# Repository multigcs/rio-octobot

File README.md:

# rio-octobot
8Axis LinuxCNC-RIO main-board - for the iceWerx iCE40-HX8K FPGA-Devboard - kicad project 
 
experimental - not fully tested yet

## software / gateware
https://github.com/multigcs/riocore

## BOM
https://eu.robotshop.com/de/products/devantech-icewerx-ice40-hx8k-fpga

https://www.amazon.de/WT32-ETH01-Embedded-Schnittstelle-Bluetooth-Entwicklungsplatine/dp/B0CW3DDWZ4

## Forum
German: https://www.cnc-aus-holz.at/index.php?thread/3130-experimente-mit-linux-cnc-auf-raspi-und-ice40-fpga-als-mesa-alternative/&postID=40335#post40335
English: https://forum.linuxcnc.org/18-computer/49142-linuxcnc-rio-realtimeio-for-linuxcnc-based-on-fpga-ice40-ecp5

## Videos

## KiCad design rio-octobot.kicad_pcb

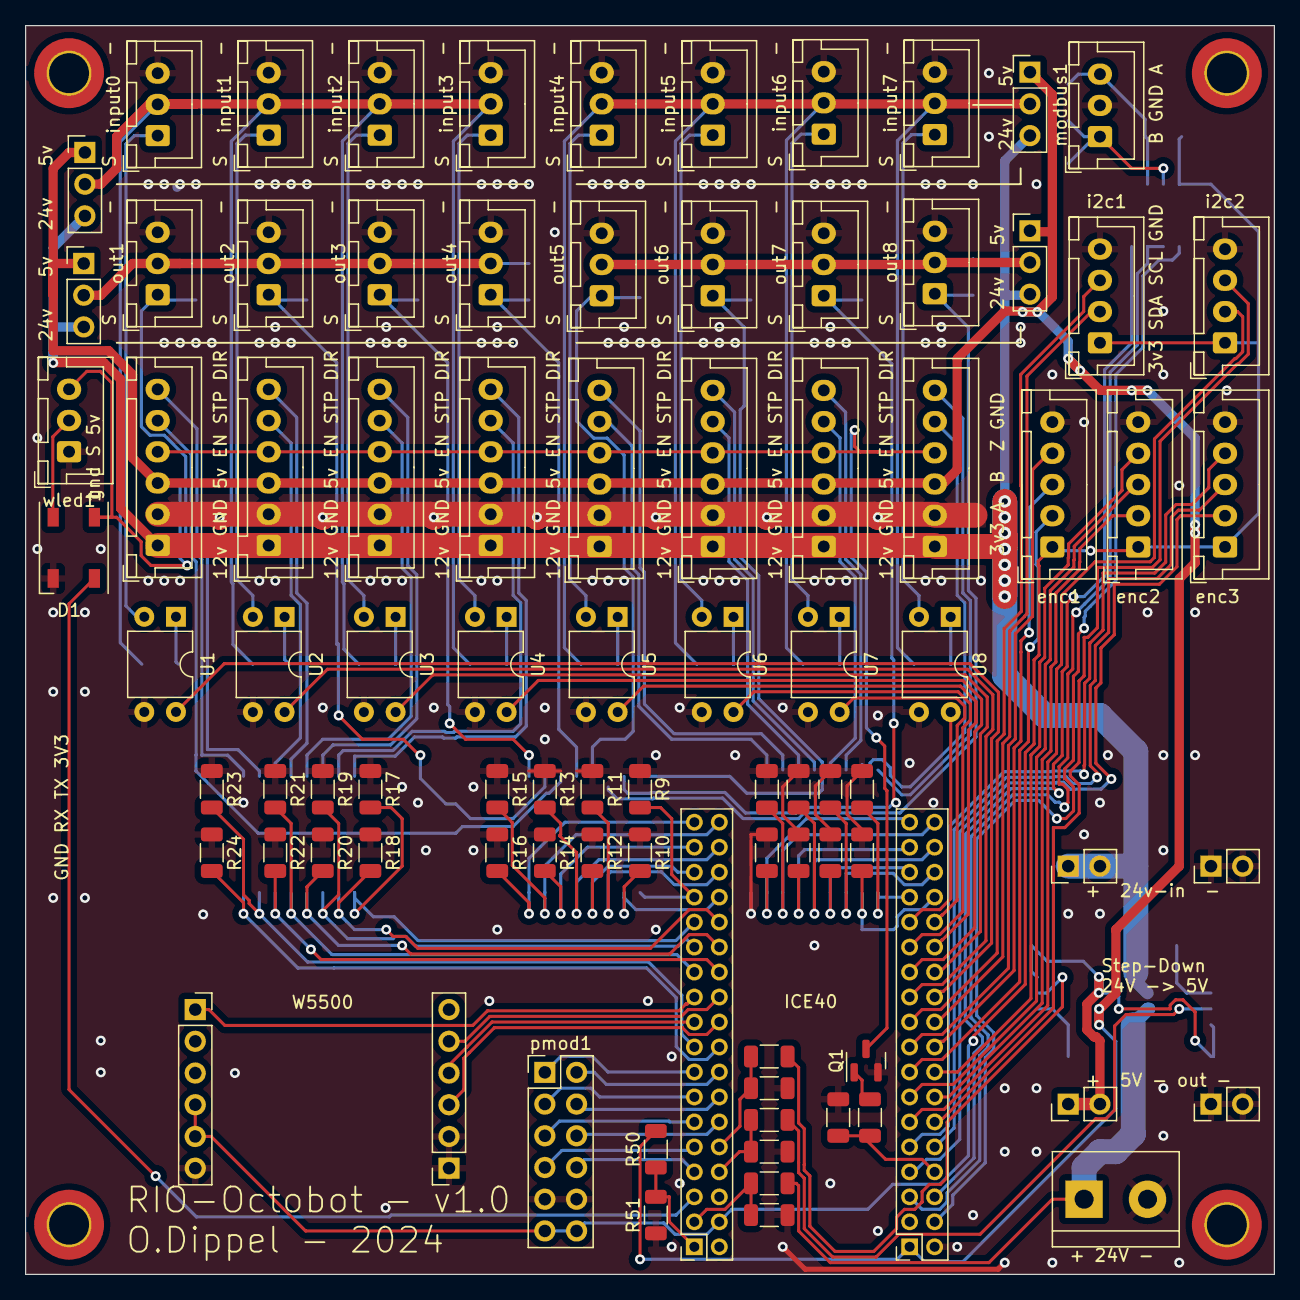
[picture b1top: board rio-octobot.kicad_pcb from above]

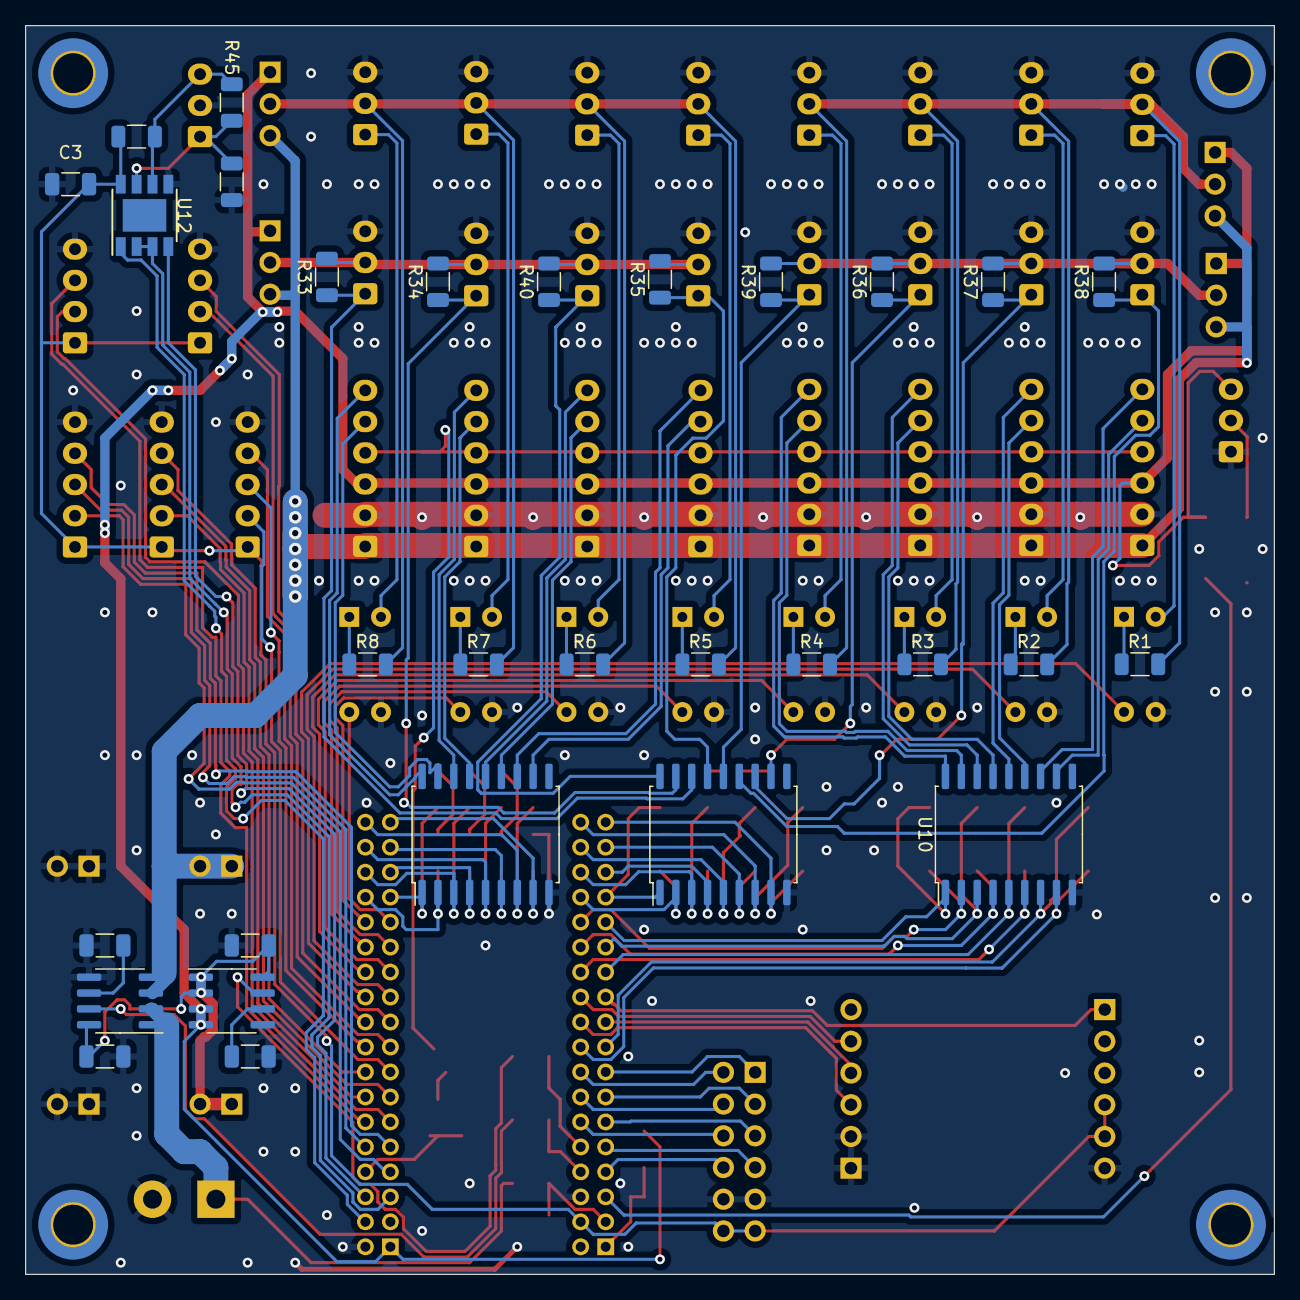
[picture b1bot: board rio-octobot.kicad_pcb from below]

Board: 2 copper layers, 100.0 x 100.0 mm, 123 parts (30 on the bottom side), 125 nets.

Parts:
+24V-1: Screw_Terminal_01x02; TerminalBlock_bornier-2_P5.08mm
C1, C4: 1n; C_1206_3216Metric
C2, C3, C5: 100n; C_1206_3216Metric
D1: WS2812B; LED_WS2812B_PLCC4_5.0x5.0mm_P3.2mm
H1, H2, H3, H4: MountingHole; MountingHole_3.2mm_M3_DIN965_Pad_TopBottom
J1, J2, J3, J4, J5, J6, J7, J8: Conn_01x06; JST_XH_B6B-XH-A_1x06_P2.50mm_Vertical
J9, J10, J11, J12: Conn_01x03; PinHeader_1x03_P2.54mm_Vertical
J15, J16: Conn_01x06; PinSocket_1x06_P2.54mm_Vertical
Q1: BC817; SOT-23
R1, R2, R3, R4, R5, R6, R7, R8, R33, R34, R35, R36, R37, R38, R39, R40: 3k3; R_1206_3216Metric
R9, R10, R11, R12, R13, R14, R15, R16, R17, R18, R19, R20, R21, R22, R23, R24, R55: 10k; R_1206_3216Metric
R25, R26, R27, R28, R29, R30, R31, R32: R; R_1206_3216Metric
R41, R44, R46, R47, R48, R50, R51, R53, R54: 20k; R_1206_3216Metric
R42, R43: 1k; R_1206_3216Metric
R45: 120; R_1206_3216Metric
U1, U2, U3, U4, U5, U6, U7, U8: PC817; DIP-4_W7.62mm
U9, U10, U11: ULN2803A; SOIC-18W_7.5x11.6mm_P1.27mm
U12: MAX485E; Diodes_SO-8EP
U13: ACS712xLCTR-20A; SOIC-8_3.9x4.9mm_P1.27mm
U14: ACS712xLCTR-5A; SOIC-8_3.9x4.9mm_P1.27mm
enc1, enc2, enc3: Conn_01x05; JST_XH_B5B-XH-A_1x05_P2.50mm_Vertical
i2c1, i2c2: Conn_01x04; JST_XH_B4B-XH-A_1x04_P2.50mm_Vertical
in+1: Conn_01x02; PinHeader_1x02_P2.54mm_Vertical
in-1: Conn_01x02; PinHeader_1x02_P2.54mm_Vertical
input0, input1, input2, input3, input4, input5, input6, input7: Conn_01x03; JST_XH_B3B-XH-A_1x03_P2.50mm_Vertical
modbus1: Conn_01x03; JST_XH_B3B-XH-A_1x03_P2.50mm_Vertical
out1, out2, out3, out4, out5, out6, out7, out8: Conn_01x03; JST_XH_B3B-XH-A_1x03_P2.50mm_Vertical
out+1: Conn_01x02; PinHeader_1x02_P2.54mm_Vertical
out-1: Conn_01x02; PinHeader_1x02_P2.54mm_Vertical
pl2, pl3: Conn_02x18_Odd_Even; PinSocket_2x18_P2.00mm_Vertical
pmod1: Conn_02x06_Odd_Even; PinHeader_2x06_P2.54mm_Vertical
wled1: Conn_01x03; JST_XH_B3B-XH-A_1x03_P2.50mm_Vertical

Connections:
3v3: C3.1, J15.4, J15.5, R46.1, U12.8 (VCC), enc1.1, enc2.1, enc3.1, i2c1.1, i2c2.1, pl2.4, pmod1.11, pmod1.12
5v: D1.1 (VDD), J1.3, J2.3, J3.3, J4.3, J5.3, J6.3, J7.3, J8.3, J9.1, J10.1, J11.1, J12.1, R50.2, U14.3 (IP-), U14.4 (IP-), pl3.1, wled1.3
12v: J1.1, J2.1, J3.1, J4.1, J5.1, J6.1, J7.1, J8.1, J9.3, J10.3, J11.3, J12.3, U13.3 (IP-), U13.4 (IP-), in+1.1, in+1.2
/input0/power: J9.2, R1.2, R2.2, R3.2, R4.2, input0.2, input1.2, input2.2, input3.2
/input4/power: J10.2, R5.2, R6.2, R7.2, R8.2, input4.2, input5.2, input6.2, input7.2
unnamed: +24V-1.1, R41.2, U13.1 (IP+), U13.2 (IP+)
unnamed: D1.2 (DOUT), wled1.2
unnamed: J1.4, J2.4, J3.4, J4.4, J5.4, J6.4, J7.4, J8.4, Q1.3 (C)
unnamed: J1.5, U10.11 (O8)
unnamed: J1.6, U10.12 (O7)
unnamed: J2.5, U10.13 (O6)
unnamed: J2.6, U10.14 (O5)
unnamed: J3.5, U10.15 (O4)
unnamed: J3.6, U10.16 (O3)
unnamed: J4.5, U10.17 (O2)
unnamed: J4.6, U10.18 (O1)
unnamed: J5.5, U11.11 (O8)
unnamed: J5.6, U11.12 (O7)
unnamed: J6.5, U11.13 (O6)
unnamed: J6.6, U11.14 (O5)
unnamed: J7.5, U11.15 (O4)
unnamed: J7.6, U11.16 (O3)
unnamed: J8.5, U11.17 (O2)
unnamed: J8.6, U11.18 (O1)
unnamed: J11.2, R36.2, R37.2, R38.2, R39.2, out1.2, out2.2, out3.2, out4.2
unnamed: J12.2, R33.2, R34.2, R35.2, R40.2, out5.2, out6.2, out7.2, out8.2
unnamed: Q1.1 (B), R43.2
unnamed: R1.1, U1.1
unnamed: R2.1, U2.1
unnamed: R3.1, U3.1
unnamed: R4.1, U4.1
unnamed: R5.1, U5.1
unnamed: R6.1, U6.1
unnamed: R7.1, U7.1
unnamed: R8.1, U8.1
unnamed: R40.1, U9.18 (O1), out6.1
unnamed: R34.1, U9.17 (O2), out7.1
unnamed: R33.1, U9.16 (O3), out8.1
unnamed: R35.1, U9.15 (O4), out5.1
unnamed: R39.1, U9.14 (O5), out4.1
unnamed: R38.1, U9.13 (O6), out1.1
unnamed: R37.1, U9.12 (O7), out2.1
unnamed: R36.1, U9.11 (O8), out3.1
unnamed: R45.1, R46.2, U12.6 (A), modbus1.3
unnamed: R44.1, R45.2, U12.7 (B), modbus1.1
unnamed: C1.1, U13.6 (FILTER)
unnamed: C2.1, C5.1, U13.8 (VCC), U14.1 (IP+), U14.2 (IP+), U14.8 (VCC), out+1.1, out+1.2
unnamed: R47.1, U13.7 (VIOUT)
unnamed: C4.1, U14.6 (FILTER)
unnamed: R53.1, U14.7 (VIOUT)
unnamed: U1.2, input0.1
unnamed: U2.2, input1.1
unnamed: U3.2, input2.1
unnamed: U4.2, input3.1
unnamed: U5.2, input4.1
unnamed: U6.2, input5.1
unnamed: U7.2, input6.1
unnamed: U8.2, input7.1
a1: R12.2, U9.4 (I4), pl2.31
a2: R11.2, U9.3 (I3), pl2.32
a3: R14.2, U9.6 (I6), pl2.33
a4: R16.2, U9.8 (I8), pl2.35
a6: R31.2, U11.7 (I7), pl3.36
a7: R32.2, U11.8 (I8), pl3.35
a10: R25.2, U11.1 (I1), pl3.29
a11: U6.4, pl3.25
a12: U5.4, pl3.26
ad1: R47.2, R48.2, pl2.8
ad2: R53.2, R54.2, pl2.10
ad3: R50.1, R51.2, pl2.1
ad4: R41.1, R42.2, pl2.3
b1: R10.2, U9.2 (I2), pl2.30
b14: U4.4, pl3.23
c1: R17.2, U10.1 (I1), pl2.27
c3: R9.2, U9.1 (I1), pl2.29
c4: R13.2, U9.5 (I5), pl2.34
c5: R15.2, U9.7 (I7), pl2.36
c6: R29.2, U11.5 (I5), pl3.34
c7: R30.2, U11.6 (I6), pl3.33
c10: U8.4, pl3.27
c11: U7.4, pl3.28
c12: U2.4, pl3.21
c14: U3.4, pl3.24
d1: R20.2, U10.4 (I4), pl2.26
d3: R18.2, U10.2 (I2), pl2.28
d6: R28.2, U11.4 (I4), pl3.31
d7: R27.2, U11.3 (I3), pl3.32
d10: R26.2, U11.2 (I2), pl3.30
d12: i2c1.3, pl3.19
d14: U1.4, pl3.22
e1: R19.2, U10.3 (I3), pl2.25
e12: enc1.4, pl3.17
e14: i2c1.2, pl3.20
f3: R22.2, U10.6 (I6), pl2.24
f12: enc1.2, pl3.15
f14: enc1.3, pl3.18
g1: R21.2, U10.5 (I5), pl2.23
g3: J16.5, pl2.22
g12: enc2.3, pl3.13
g14: enc2.4, pl3.16
gnd: +24V-1.2, C1.2, C2.2, C3.2, C4.2, C5.2, D1.3 (VSS), J1.2, J2.2, J3.2, J4.2, J5.2, J6.2, J7.2, J8.2, J15.6, J16.1, J16.2, Q1.2 (E), R9.1, R10.1, R11.1, R12.1, R13.1, R14.1, R15.1, R16.1, R17.1, R18.1, R19.1, R20.1, R21.1, R22.1, R23.1, R24.1, R25.1, R26.1, R27.1, R28.1, R29.1, R30.1, R31.1, R32.1, R42.1, R44.2, R48.1, R51.1, R54.1, R55.1, U1.3, U2.3, U3.3, U4.3, U5.3, U6.3, U7.3, U8.3, U9.9 (GND), U10.9 (GND), U11.9 (GND), U12.5 (GND), U13.5 (GND), U14.5 (GND), enc1.5, enc2.5, enc3.5, i2c1.4, i2c2.4, in-1.1, in-1.2, input0.3, input1.3, input2.3, input3.3, input4.3, input5.3, input6.3, input7.3, modbus1.2, out1.3, out2.3, out3.3, out4.3, out5.3, out6.3, out7.3, out8.3, out-1.1, out-1.2, pl2.6, pl3.2, pmod1.9, pmod1.10, wled1.1
h1: J15.1, pl2.21
h3: J16.3, pl2.20
h11: enc3.4, pl3.9
h12: enc2.2, pl3.14
j1: J16.4, pl2.19
j3: R24.2, U10.8 (I8), pl2.18
j12: i2c2.2, pl3.11
k3: R23.2, U10.7 (I7), pl2.17
k12: enc3.2, pl3.7
k14: i2c2.3, pl3.12
l1: pl2.16, pmod1.2
l12: R43.1, R55.2, pl3.8
l14: enc3.3, pl3.10
m1: pl2.15, pmod1.1
m3: pl2.13, pmod1.3
m6: pl2.7, pmod1.8
m7: D1.4 (DIN), pl2.5
n1: pl2.14, pmod1.4
n14: U12.2 (~RE), U12.3 (DE), pl3.5
p1: pl2.12, pmod1.6
p2: pl2.11, pmod1.5
p3: pl2.9, pmod1.7
p8: U12.1 (RO), pl3.4
p14: U12.4 (DI), pl3.6

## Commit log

2024-07-03 initial release
2024-07-03 adding image
2024-07-10 fixing labels / add some values
2024-07-12 adding vid to readme
2024-07-17 removing level shifter from wled
2024-08-10 chaning network interface to W5500
